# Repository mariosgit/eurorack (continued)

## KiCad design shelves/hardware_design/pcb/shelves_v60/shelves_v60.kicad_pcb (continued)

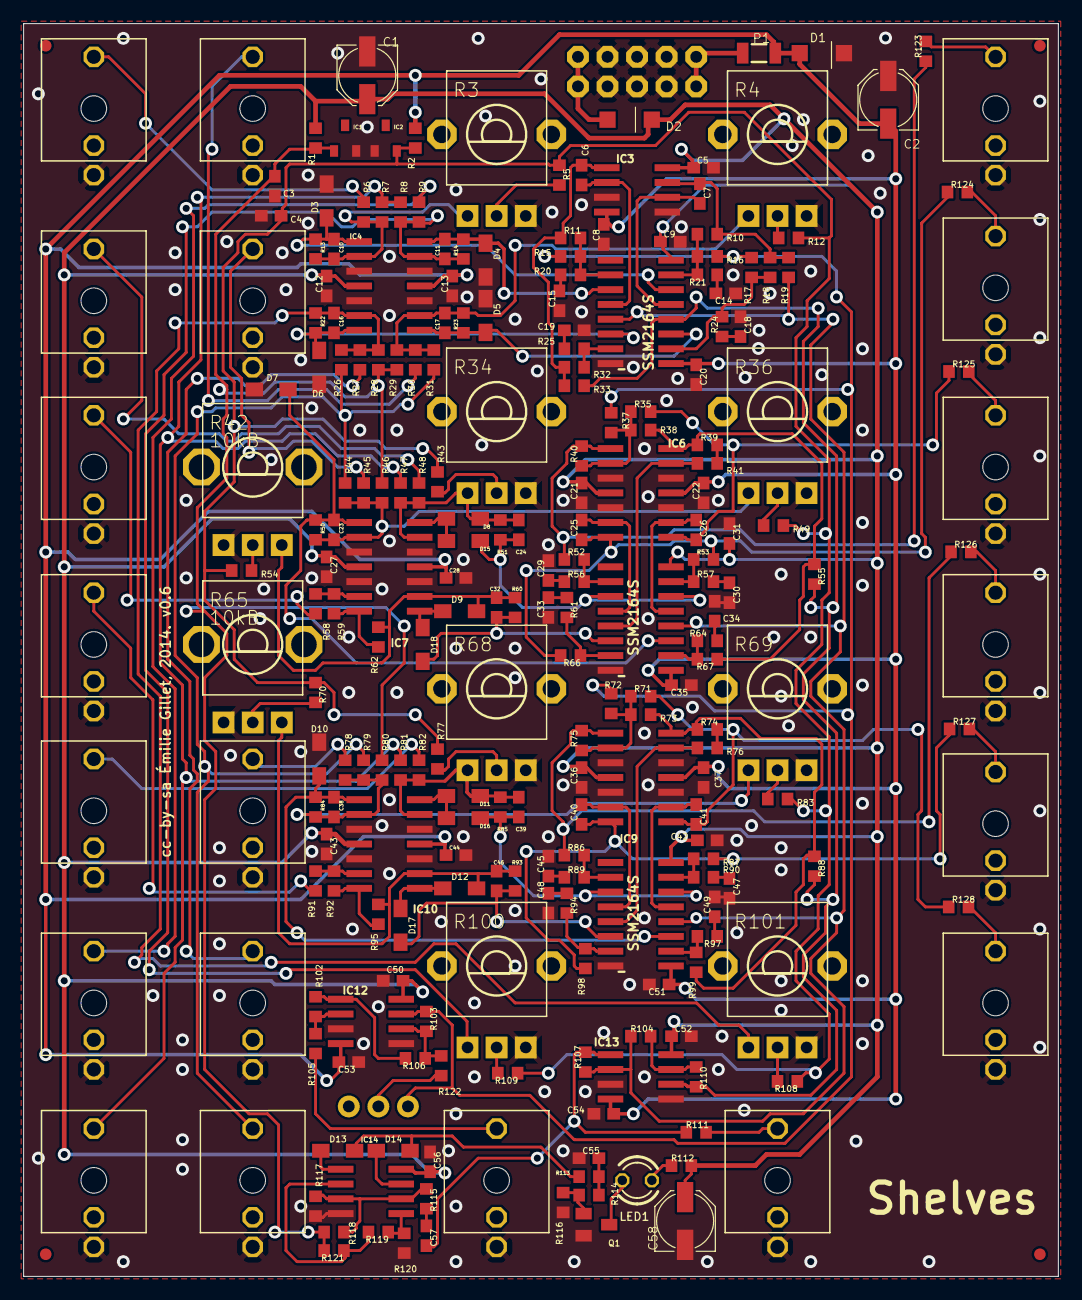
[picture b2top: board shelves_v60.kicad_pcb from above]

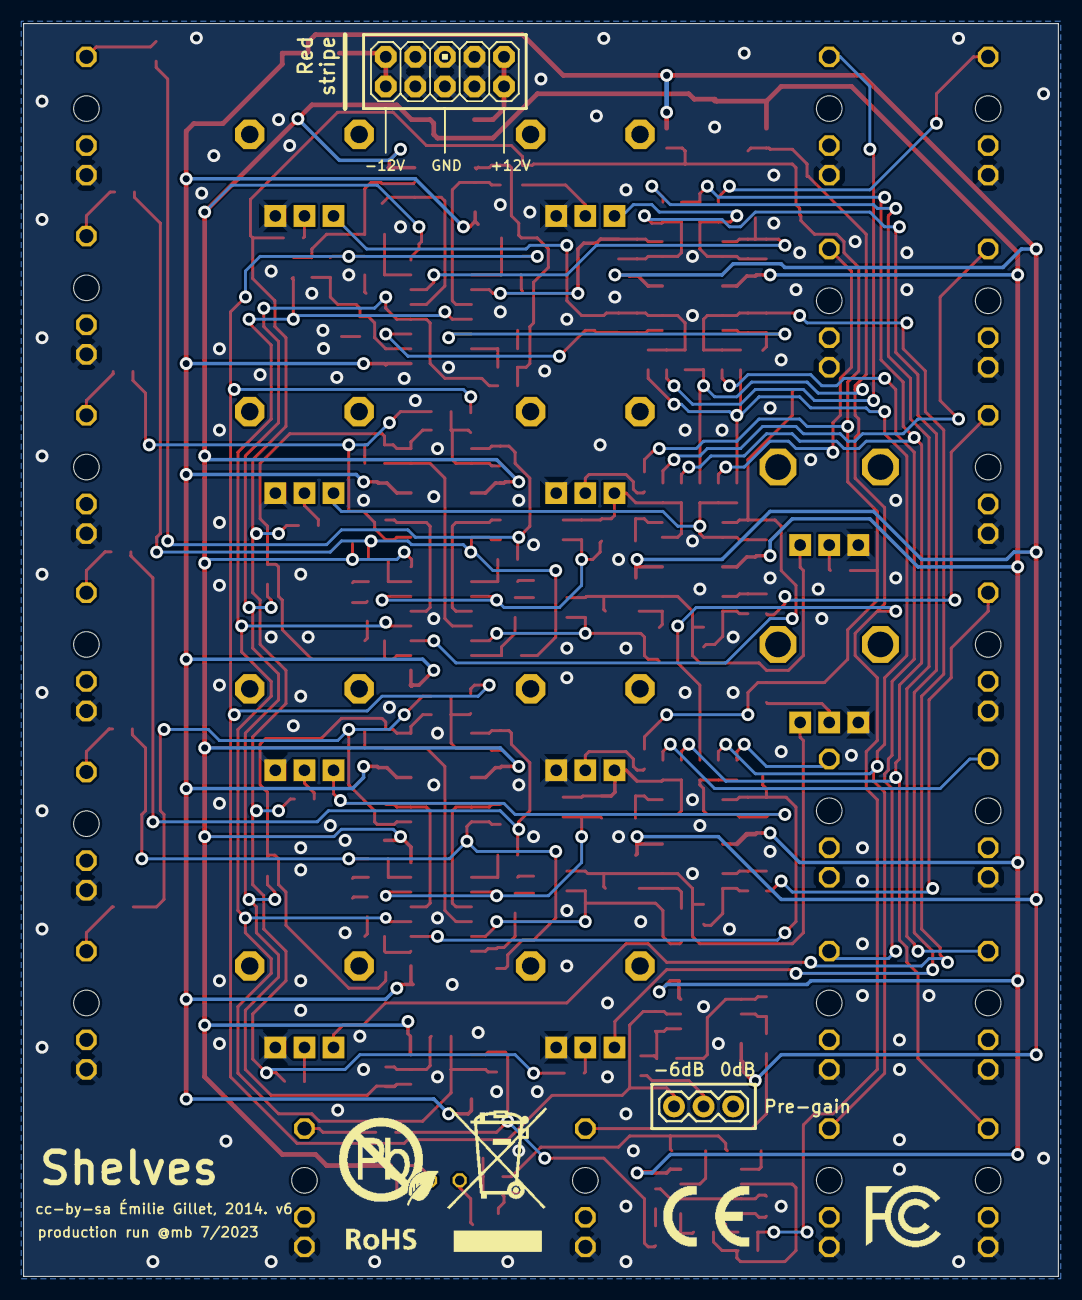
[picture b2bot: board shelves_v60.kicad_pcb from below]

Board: 2 copper layers, 88.9 x 107.6 mm, 248 parts (5 on the bottom side), 131 nets.

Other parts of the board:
U$1: FCC_MEDIUM
U$2: ROHS_BIG
U$3: CE_MEDIUM

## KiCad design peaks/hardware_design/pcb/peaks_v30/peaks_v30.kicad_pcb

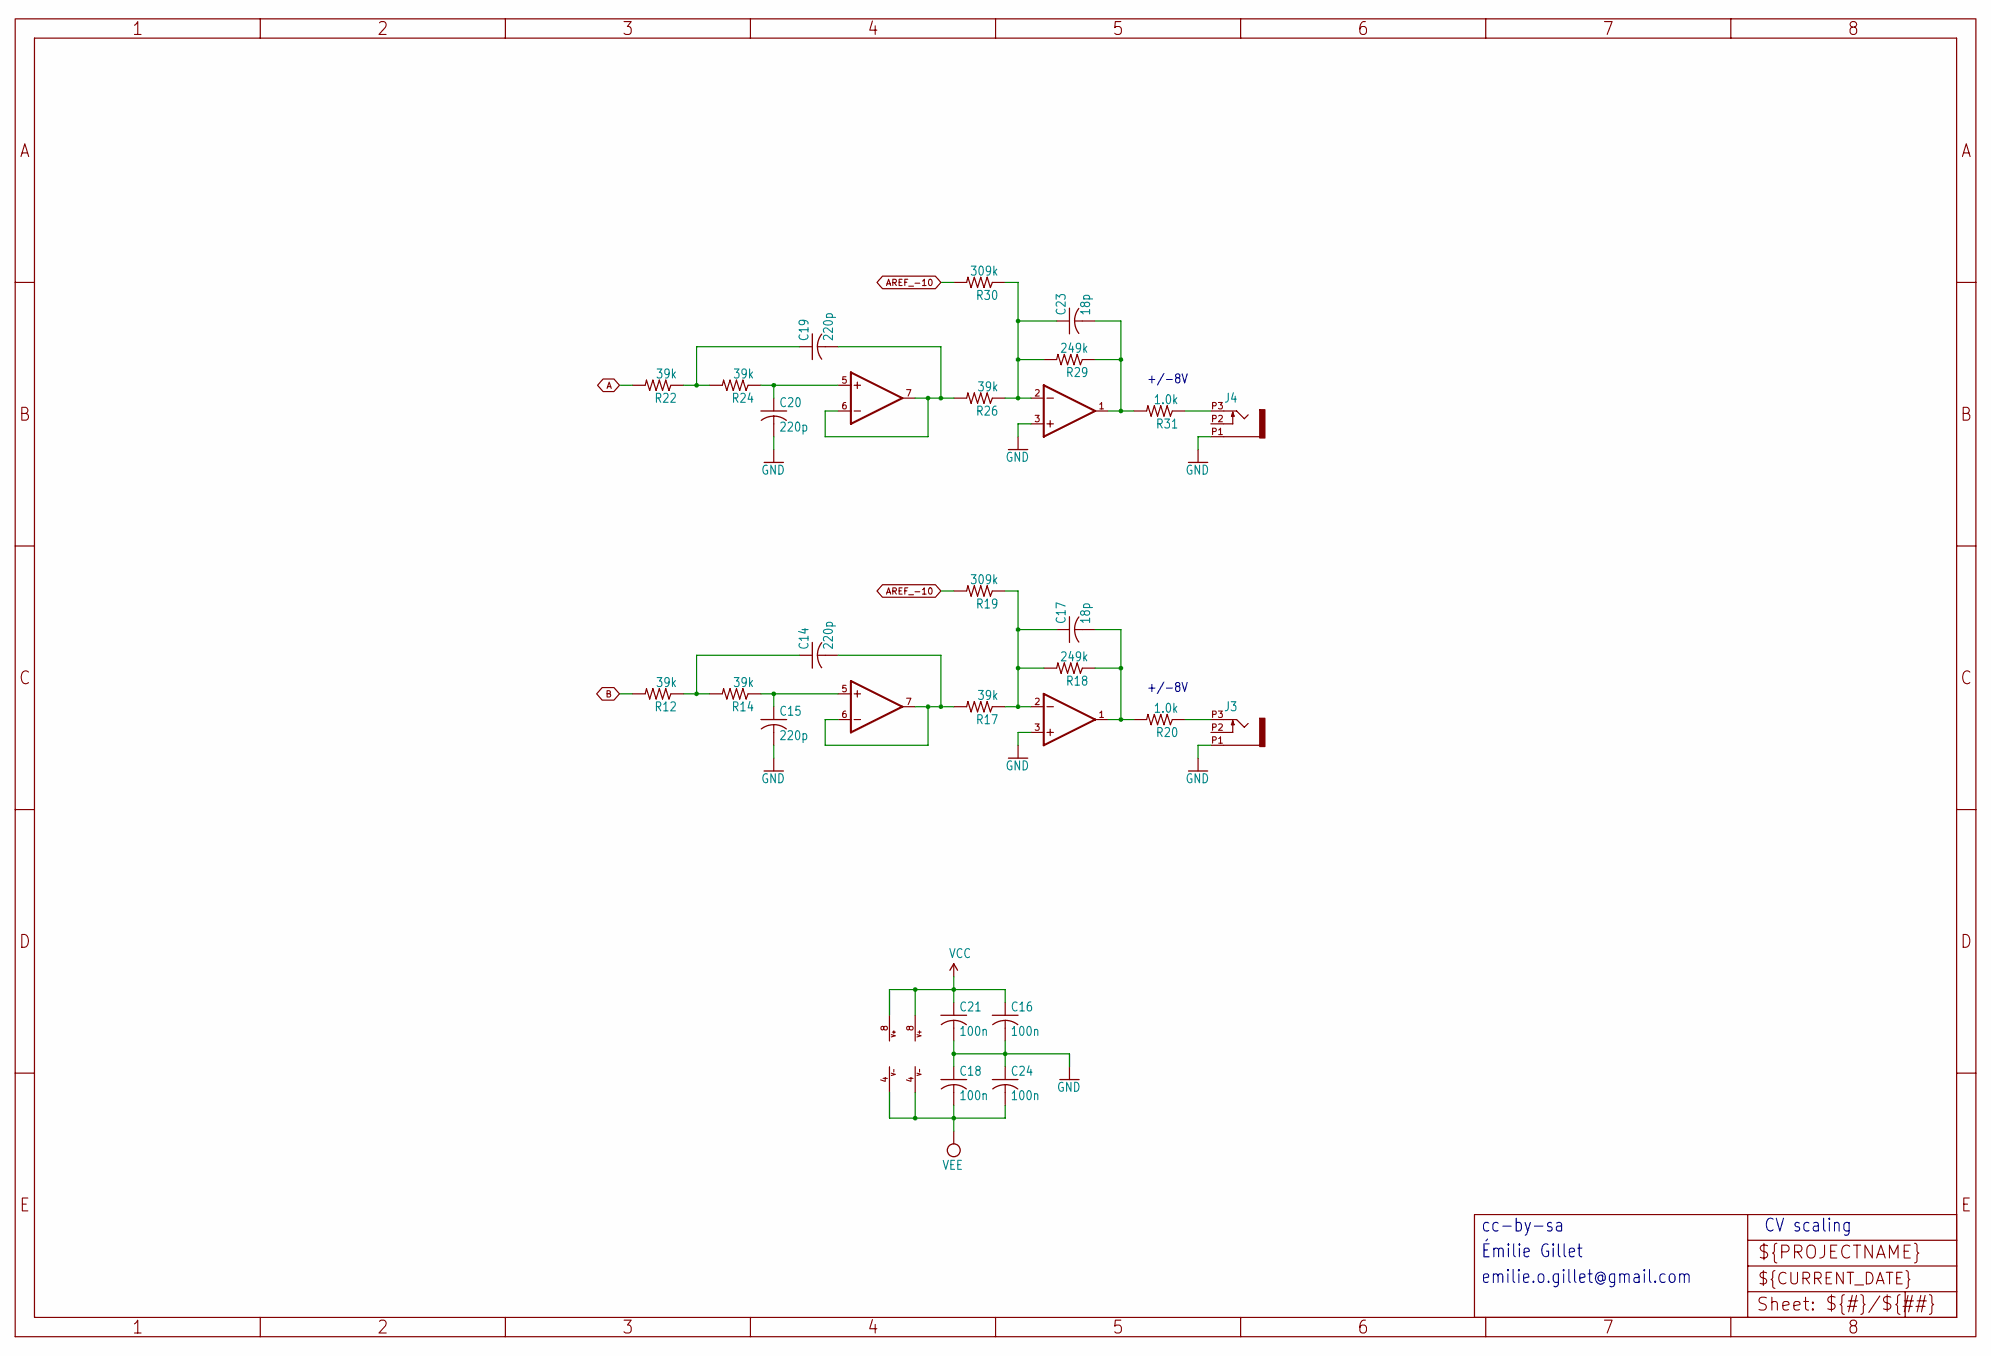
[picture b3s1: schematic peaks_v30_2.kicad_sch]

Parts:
C14, C15, C19, C20: 220p; C0603
C16, C18, C21, C24: 100n; C0603
C17, C23: 18p; C0603
IC4, IC5: TL072D; SO08
J3, J4: PJ301_THONKICONN6; WQP_PJ_301M6
R12, R14, R17, R22, R24, R26: 39k; R0603
R18, R29: 249k; R0603
R19, R30: 309k; R0603
R20, R31: 1.0k; R0603

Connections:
A: R22.2; also elsewhere on the board
AREF_-10: R19.2, R30.2; also elsewhere on the board
B: R12.2; also elsewhere on the board
GND: C15.2, C16.2, C18.1, C20.2, C21.2, C24.1, IC4.3 (+IN), IC5.3 (+IN), J3.P1 (1), J4.P1 (1); also elsewhere on the board
unnamed: C14.1, R12.1, R14.2
unnamed: C19.1, R22.1, R24.2
unnamed: C17.1, IC4.2 (-IN), R17.1, R18.2, R19.1
unnamed: C17.2, IC4.1 (OUT), R18.1, R20.2
unnamed: C15.1, IC4.5 (+IN), R14.1
unnamed: C14.2, IC4.6 (-IN), IC4.7 (OUT), R17.2
unnamed: C23.1, IC5.2 (-IN), R26.1, R29.2, R30.1
unnamed: C23.2, IC5.1 (OUT), R29.1, R31.2
unnamed: C20.1, IC5.5 (+IN), R24.1
unnamed: C19.2, IC5.6 (-IN), IC5.7 (OUT), R26.2
unnamed: J3.P3 (3), R20.1
unnamed: J4.P3 (3), R31.1
VCC: C16.1, C21.1, IC4.8 (V+), IC5.8 (V+); also elsewhere on the board
VEE: C18.2, C24.2, IC4.4 (V-), IC5.4 (V-); also elsewhere on the board

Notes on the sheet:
CV scaling
emilie.o.gillet@gmail.com
+/-8V
cc-by-sa
Émilie Gillet

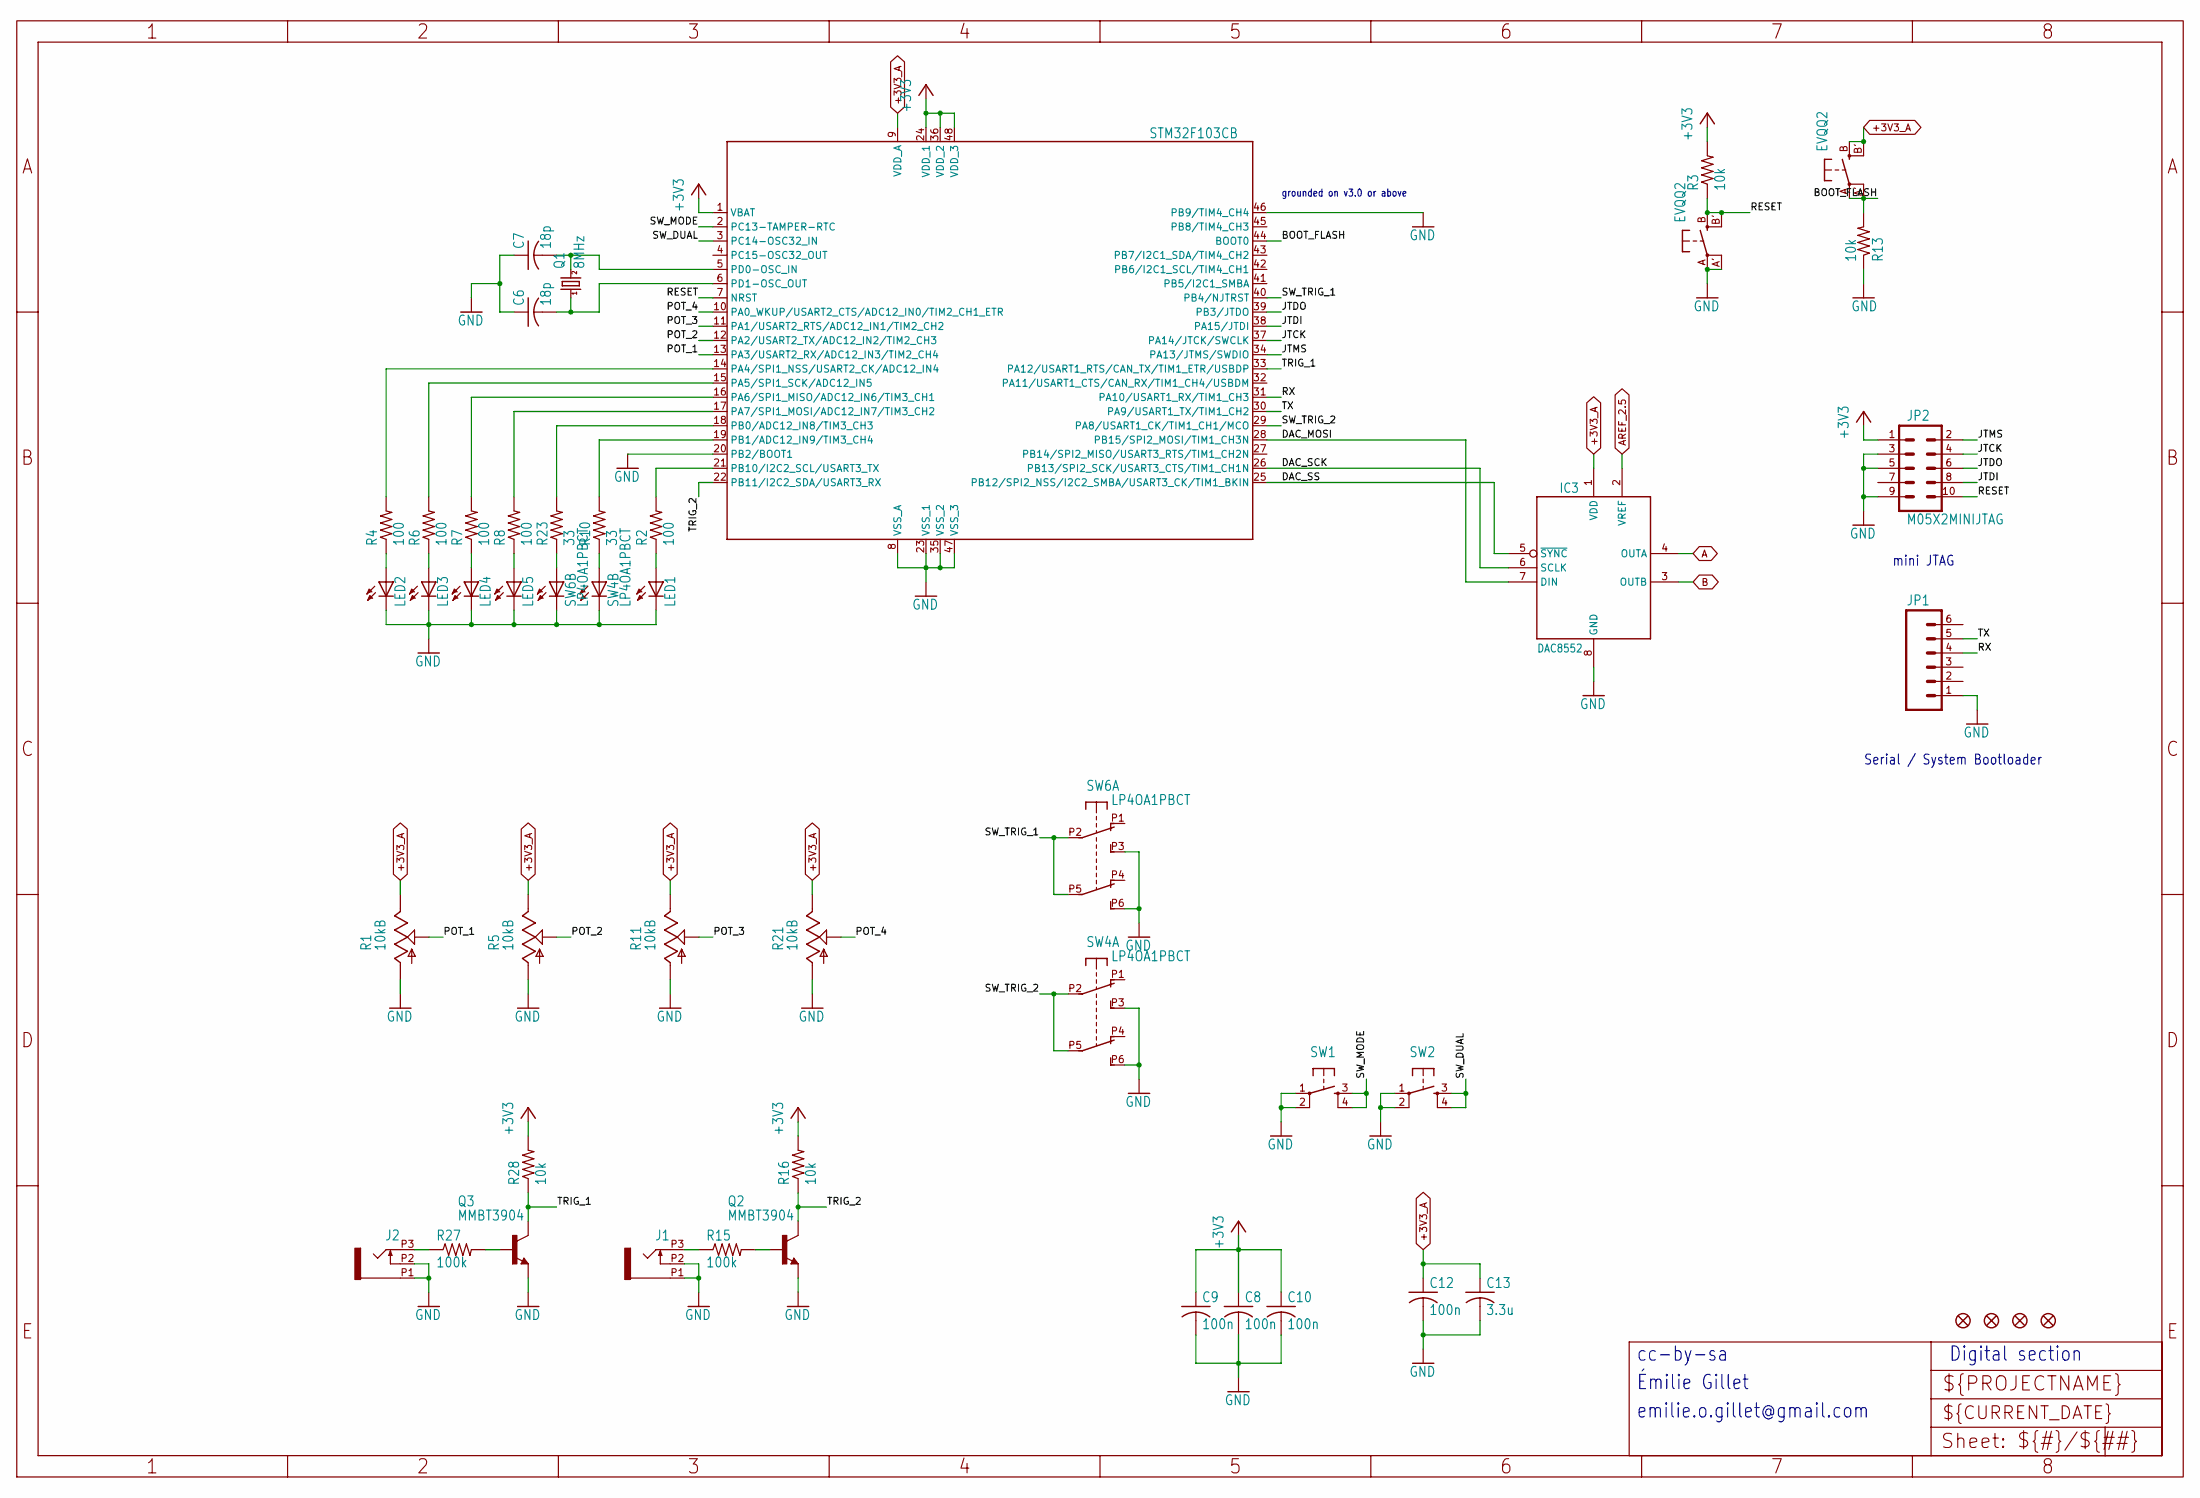
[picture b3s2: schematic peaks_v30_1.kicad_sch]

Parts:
C6, C7: 18p; C0603
C8, C9, C10, C12: 100n; C0603
C13: 3.3u; C0603
F1, F2, F3, F4: FIDUCIAL1X2; FIDUCIAL-1X2
IC3: DAC8552; MSOP-8
J1, J2: PJ301_THONKICONN6; WQP_PJ_301M6
JP1: M06SIP; 1X06
JP2: M05X2MINIJTAG; 2X5-1.27
LED1, LED2, LED3, LED4, LED5: LED3MM
Q1: 8MHz; HC49UP
Q2, Q3: MMBT3904; SOT23-BEC
R1, R5, R11, R21: 10kB; ALPS_POT_VERTICAL_PS
R2, R4, R6, R7, R8: 100; R0603
R3, R13, R16, R28: 10k; R0603
R10, R23: 33; R0603
R15, R27: 100k; R0603
SW1, SW2: TAC_SWITCHPTH; TACTILE-PTH
SW3, SW5: EVQQ2; EVQ-Q2
SW4, SW6: LP4OA1PBCT
UC1: STM32F103CB; LQFP48

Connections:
+3V3: C8.1, C9.1, C10.1, JP2.1, R3.2, R16.2, R28.2, UC1.1 (VBAT), UC1.24 (VDD_1), UC1.36 (VDD_2), UC1.48 (VDD_3); also elsewhere on the board
+3V3_A: C12.1, C13.1, IC3.1 (VDD), R1.P$1 (E), R5.P$1 (E), R11.P$1 (E), R21.P$1 (E), SW5.B (S), SW5.B' (S1), UC1.9 (VDD_A); also elsewhere on the board
/peaks_v30_1/BOOT_FLASH: R13.2, SW5.A, SW5.A' (P1), UC1.44 (BOOT0)
/peaks_v30_1/DAC_MOSI: IC3.7 (DIN), UC1.28 (PB15/SPI2_MOSI/TIM1_CH3N)
/peaks_v30_1/DAC_SCK: IC3.6 (SCLK), UC1.26 (PB13/SPI2_SCK/USART3_CTS/TIM1_CH1N)
/peaks_v30_1/DAC_SS: IC3.5 (~SYNC), UC1.25 (PB12/SPI2_NSS/I2C2_SMBA/USART3_CK/TIM1_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)
/peaks_v30_1/JTCK: JP2.4, UC1.37 (PA14/JTCK/SWCLK)
/peaks_v30_1/JTDI: JP2.8, UC1.38 (PA15/JTDI)
/peaks_v30_1/JTDO: JP2.6, UC1.39 (PB3/JTDO)
/peaks_v30_1/JTMS: JP2.2, UC1.34 (PA13/JTMS/SWDIO)
/peaks_v30_1/POT_1: R1.P$2 (S), UC1.13 (PA3/USART2_RX/ADC12_IN3/TIM2_CH4)
/peaks_v30_1/POT_2: R5.P$2 (S), UC1.12 (PA2/USART2_TX/ADC12_IN2/TIM2_CH3)
/peaks_v30_1/POT_3: R11.P$2 (S), UC1.11 (PA1/USART2_RTS/ADC12_IN1/TIM2_CH2)
/peaks_v30_1/POT_4: R21.P$2 (S), UC1.10 (PA0_WKUP/USART2_CTS/ADC12_IN0/TIM2_CH1_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)
/peaks_v30_1/RESET: JP2.10, R3.1, SW3.B (S), SW3.B' (S1), UC1.7 (NRST)
/peaks_v30_1/RX: JP1.4, UC1.31 (PA10/USART1_RX/TIM1_CH3)
/peaks_v30_1/SW_DUAL: SW2.3, SW2.4, UC1.3 (PC14-OSC32_IN)
/peaks_v30_1/SW_MODE: SW1.3, SW1.4, UC1.2 (PC13-TAMPER-RTC)
/peaks_v30_1/SW_TRIG_1: SW6.P2 (A2), SW6.P5 (B2), UC1.40 (PB4/NJTRST)
/peaks_v30_1/SW_TRIG_2: SW4.P2 (A2), SW4.P5 (B2), UC1.29 (PA8/USART1_CK/TIM1_CH1/MCO)
/peaks_v30_1/TRIG_1: Q3.C, R28.1, UC1.33 (PA12/USART1_RTS/CAN_TX/TIM1_ETR/USBDP)
/peaks_v30_1/TRIG_2: Q2.C, R16.1, UC1.22 (PB11/I2C2_SDA/USART3_RX)
/peaks_v30_1/TX: JP1.5, UC1.30 (PA9/USART1_TX/TIM1_CH2)
A: IC3.4 (OUTA); also elsewhere on the board
AREF_2.5: IC3.2 (VREF); also elsewhere on the board
B: IC3.3 (OUTB); also elsewhere on the board
GND: C6.1, C7.1, C8.2, C9.2, C10.2, C12.2, C13.2, IC3.8 (GND), J1.P1 (1), J1.P2 (2), J2.P1 (1), J2.P2 (2), JP1.1, JP2.3, JP2.5, JP2.9, LED1.K (C), LED2.K (C), LED3.K (C), LED4.K (C), LED5.K (C), Q2.E, Q3.E, R1.P$3 (A), R5.P$3 (A), R11.P$3 (A), R13.1, R21.P$3 (A), SW1.1, SW1.2, SW2.1, SW2.2, SW3.A, SW3.A' (P1), SW4.L2, SW4.P3 (A3), SW4.P6 (B3), SW6.L2, SW6.P3 (A3), SW6.P6 (B3), UC1.8 (VSS_A), UC1.20 (PB2/BOOT1), UC1.23 (VSS_1), UC1.35 (VSS_2), UC1.46 (PB9/TIM4_CH4), UC1.47 (VSS_3); also elsewhere on the board
unnamed: J1.P3 (3), R15.1
unnamed: J2.P3 (3), R27.1
unnamed: LED1.A, R2.1
unnamed: LED2.A, R4.1
unnamed: LED3.A, R6.1
unnamed: LED4.A, R7.1
unnamed: LED5.A, R8.1
unnamed: Q2.B, R15.2
unnamed: Q3.B, R27.2
unnamed: R10.1, SW4.L1
unnamed: R23.1, SW6.L1
unnamed: R4.2, UC1.14 (PA4/SPI1_NSS/USART2_CK/ADC12_IN4)
unnamed: R6.2, UC1.15 (PA5/SPI1_SCK/ADC12_IN5)
unnamed: R7.2, UC1.16 (PA6/SPI1_MISO/ADC12_IN6/TIM3_CH1)
unnamed: R8.2, UC1.17 (PA7/SPI1_MOSI/ADC12_IN7/TIM3_CH2)
unnamed: R23.2, UC1.18 (PB0/ADC12_IN8/TIM3_CH3)
unnamed: R10.2, UC1.19 (PB1/ADC12_IN9/TIM3_CH4)
unnamed: R2.2, UC1.21 (PB10/I2C2_SCL/USART3_TX)
unnamed: C7.2, Q1.2, UC1.5 (PD0-OSC_IN)
unnamed: C6.2, Q1.1, UC1.6 (PD1-OSC_OUT)

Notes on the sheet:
Digital section
cc-by-sa
Émilie Gillet
emilie.o.gillet@gmail.com
Serial / System Bootloader
mini JTAG
grounded on v3.0 or above

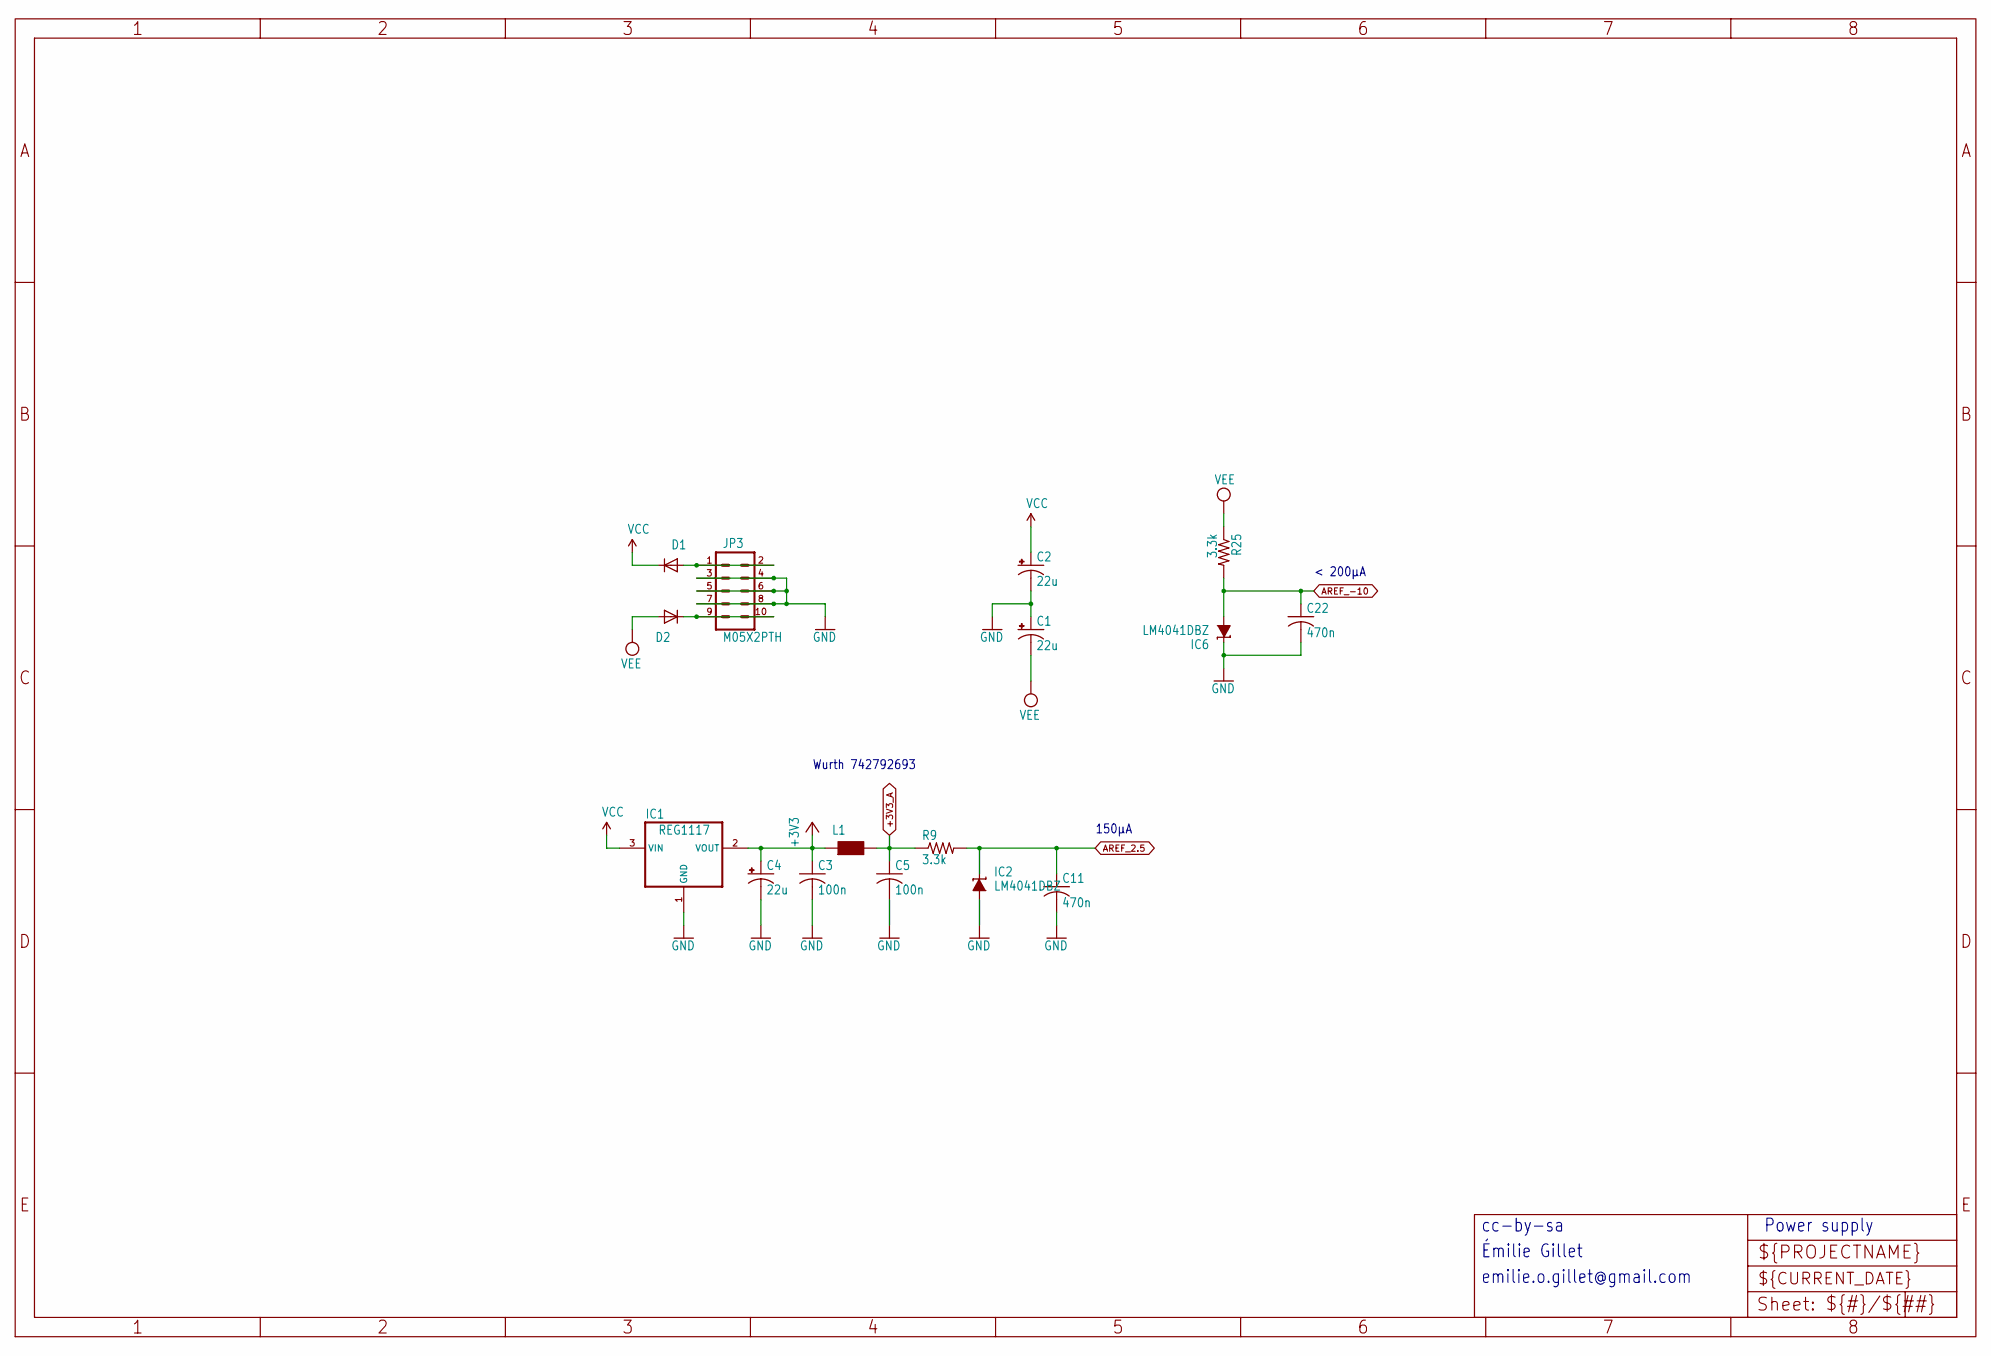
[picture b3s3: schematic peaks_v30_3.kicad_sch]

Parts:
C1, C2, C4: 22u; PANASONIC_C
C3, C5: 100n; C0603
C11, C22: 470n; C0603
D1, D2: 1N5819HW; SOD123
IC1: REG1117; SOT223
IC2, IC6: LM4041DBZ; DBZ_R-PDSO-G3
JP3: M05X2PTH; AVR_ICSP
L1: WE-CBF_0603; 0603
R9, R25: 3.3k; R0603

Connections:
+3V3: C3.1, C4.+, IC1.2 (VOUT), L1.1; also elsewhere on the board
+3V3_A: C5.1, L1.2, R9.1; also elsewhere on the board
AREF_2.5: C11.1, IC2.1 (C), R9.2; also elsewhere on the board
AREF_-10: C22.1, IC6.2 (A), R25.2; also elsewhere on the board
GND: C1.+, C2.-, C3.2, C4.-, C5.2, C11.2, C22.2, IC1.1 (GND), IC2.2 (A), IC6.1 (C), JP3.3, JP3.4, JP3.5, JP3.6, JP3.7, JP3.8; also elsewhere on the board
unnamed: D1.A, JP3.1, JP3.2
unnamed: D2.C, JP3.9, JP3.10
VCC: C2.+, D1.C, IC1.3 (VIN); also elsewhere on the board
VEE: C1.-, D2.A, R25.1; also elsewhere on the board

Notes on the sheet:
Émilie Gillet
Wurth 742792693
Power supply
150µA
cc-by-sa
emilie.o.gillet@gmail.com
< 200µA

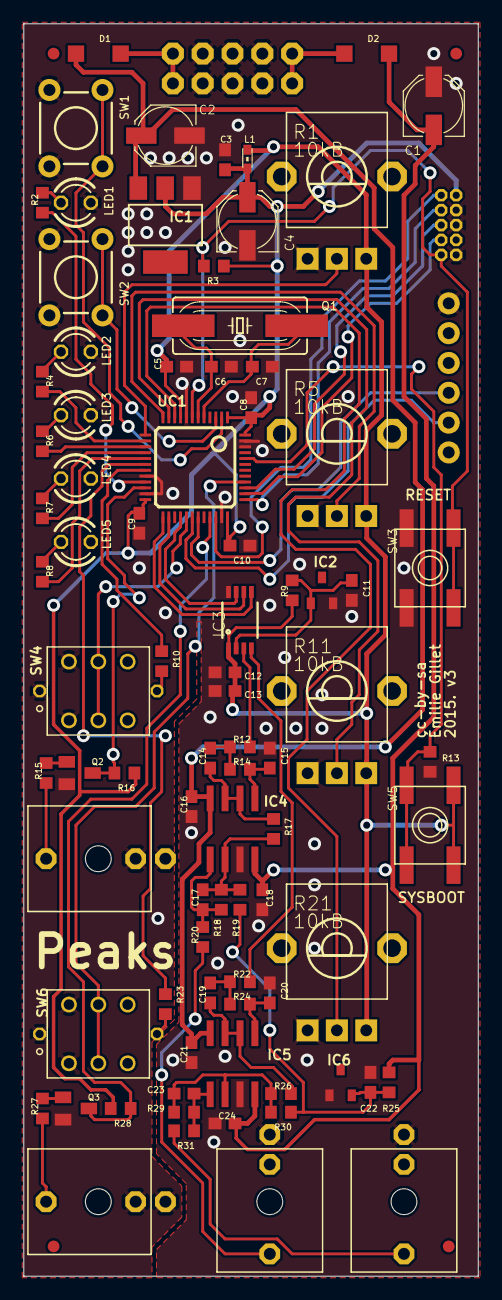
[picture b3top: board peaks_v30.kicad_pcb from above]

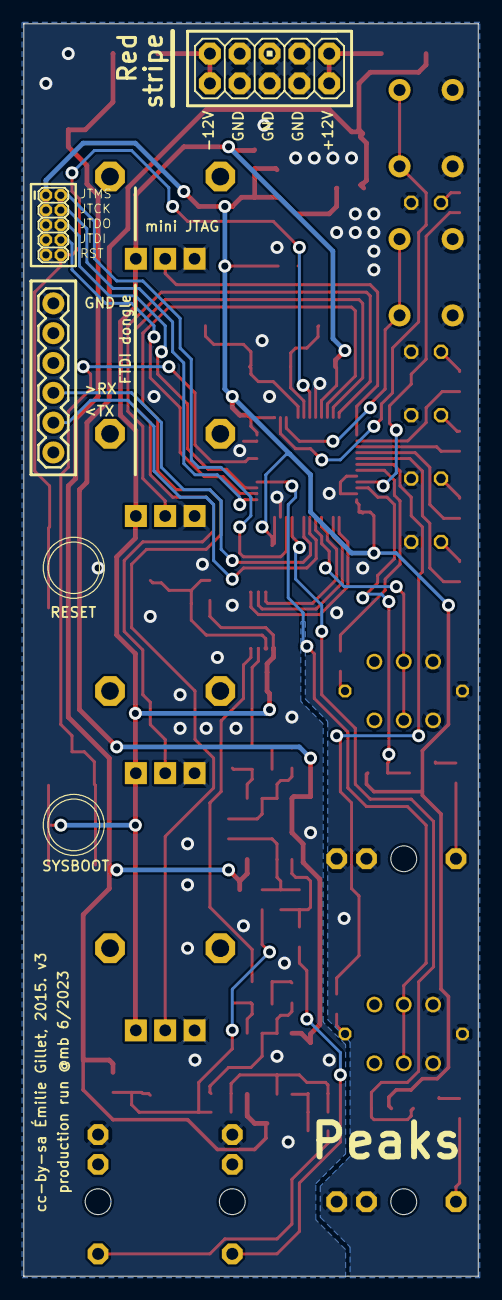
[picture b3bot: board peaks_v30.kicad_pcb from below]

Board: 2 copper layers, 38.7 x 106.7 mm, 90 parts (3 on the bottom side), 64 nets.

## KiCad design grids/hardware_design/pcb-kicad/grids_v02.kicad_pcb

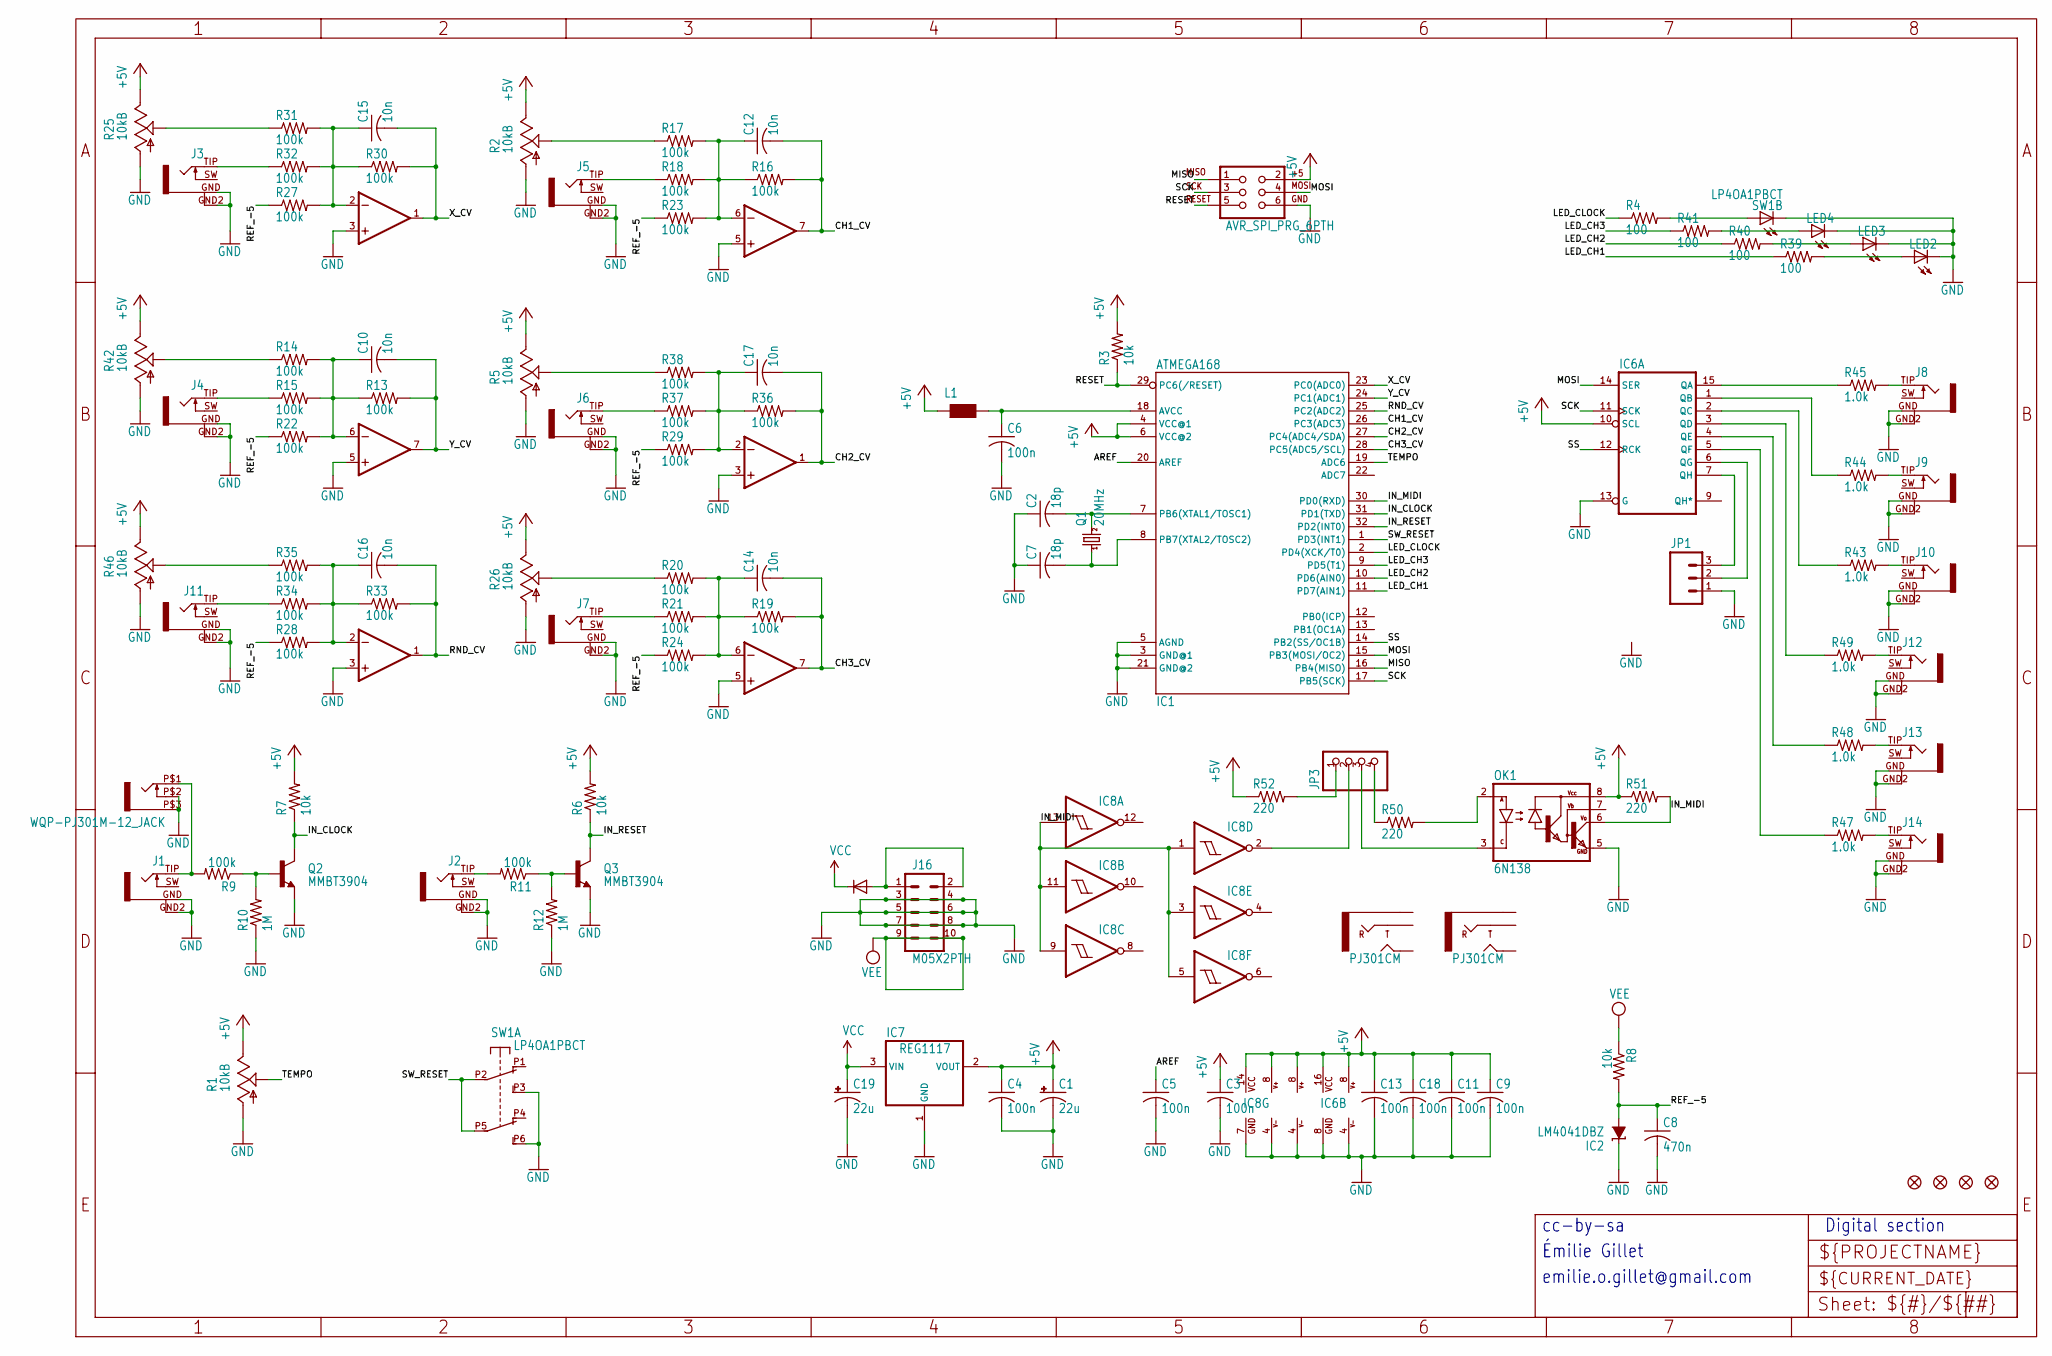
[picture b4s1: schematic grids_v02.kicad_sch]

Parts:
C1, C19: 22u; PANASONIC_C
C2, C7: 18p; C0603
C3, C4, C5, C6, C9, C11, C13, C18: 100n; C0603
C8: 470n; C0603
C10, C12, C14, C15, C16, C17: 10n; C0603
D1: 1N5819HW; SOD123
F1, F2, F3, F4: FIDUCIAL1X2; FIDUCIAL-1X2
IC1: ATMEGA168; TQFP32-08
IC2: LM4041DBZ; DBZ_R-PDSO-G3
IC3, IC4, IC5: TL072D; SO08
IC6: 74595D; SO16
IC7: REG1117; SOT223
IC8: 7414D; SO14
J1, J2, J3, J4, J5, J6, J7, J8, J9, J10, J11, J12, J13, J14: PJ301WQP; WQP_PJ_301BM
J15: AVR_SPI_PRG_6PTH; 2X3
J16: M05X2PTH; AVR_ICSP
JP1: M03PTH; 1X03
JP3: PINHD-1X4; 1X04
L1: WE-CBF_0603; 0603
LED2, LED3, LED4: LED3MM
OK1: 6N138; DIL08
Q1: 20MHz; HC49UP
Q2, Q3: MMBT3904; SOT23-BEC
R1, R2, R5, R25, R26, R46: 10kB; ALPS_POT_VERTICAL_PS
R3, R6, R7, R8: 10k; R0603
R4, R39, R40, R41: 100; R0603
R9, R11, R13, R14, R15, R16, R17, R18, R19, R20, R21, R22, R23, R24, R27, R28, R29, R30, R31, R32, R33, R34, R35, R36, R37, R38: 100k; R0603
R10, R12: 1M; R0603
R42: 10kB; ALPS_POT_VERTICAL_PS4
R43, R44, R45, R47, R48, R49: 1.0k; R0603
R50, R51, R52: 220; R0603
SW1: LP4OA1PBCT
U$1, U$3: PJ301CM
U$4: WQP-PJ301M-12_JACK

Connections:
+5V: C1.+, C3.1, C4.1, C9.1, C11.1, C13.1, C18.1, IC1.4 (VCC@1), IC1.6 (VCC@2), IC3.8 (V+), IC4.8 (V+), IC5.8 (V+), IC6.10 (SCL), IC6.16 (VCC), IC7.2 (VOUT), IC8.14 (VCC), J15.2, L1.1, OK1.8 (VCC), R1.P$1 (E), R2.P$1 (E), R3.2, R5.P$1 (E), R6.2, R7.2, R25.P$1 (E), R26.P$1 (E), R42.P$1 (E), R46.P$1 (E), R51.1, R52.1
AREF: C5.1, IC1.20 (AREF)
CH1_CV: C12.2, IC1.26 (PC3(ADC3)), IC4.7 (OUT), R16.2
CH2_CV: C17.2, IC1.27 (PC4(ADC4/SDA)), IC5.1 (OUT), R36.2
CH3_CV: C14.2, IC1.28 (PC5(ADC5/SCL)), IC5.7 (OUT), R19.2
CLOCK_OUT: IC6.6 (QG), JP1.2
GATE1_IN: J1.TIP (2), R9.2, U$4.P$1 (2)
GATE1_LED: R4.2, SW1.L1
GATE2_IN: J2.TIP (2), R11.2
GATE2_LED: LED4.A, R41.2
GATE3_LED: LED3.A, R40.2
GATE4_LED: LED2.A, R39.2
GND: C1.-, C2.1, C3.2, C4.2, C5.2, C6.2, C7.1, C8.2, C9.2, C11.2, C13.2, C18.2, C19.-, IC1.3 (GND@1), IC1.5 (AGND), IC1.21 (GND@2), IC2.1 (C), IC3.3 (+IN), IC3.4 (V-), IC3.5 (+IN), IC4.3 (+IN), IC4.4 (V-), IC4.5 (+IN), IC5.3 (+IN), IC5.4 (V-), IC5.5 (+IN), IC6.8 (GND), IC6.13 (G), IC7.1 (GND), IC8.7 (GND), J1.GND (1), J1.GND2 (4), J2.GND (1), J2.GND2 (4), J3.GND (1), J3.GND2 (4), J4.GND (1), J4.GND2 (4), J5.GND (1), J5.GND2 (4), J6.GND (1), J6.GND2 (4), J7.GND (1), J7.GND2 (4), J8.GND (1), J8.GND2 (4), J9.GND (1), J9.GND2 (4), J10.GND (1), J10.GND2 (4), J11.GND (1), J11.GND2 (4), J12.GND (1), J12.GND2 (4), J13.GND (1), J13.GND2 (4), J14.GND (1), J14.GND2 (4), J15.6, J16.3, J16.4, J16.5, J16.6, J16.7, J16.8, JP1.1, LED2.K (C), LED3.K (C), LED4.K (C), OK1.5 (GND), Q2.E, Q3.E, R1.P$3 (A), R2.P$3 (A), R5.P$3 (A), R10.1, R12.1, R25.P$3 (A), R26.P$3 (A), R42.P$3 (A), R46.P$3 (A), SW1.L2, SW1.P3 (A3), SW1.P6 (B3), U$4.P$2 (3), U$4.P$3 (1)
IN_CLOCK: IC1.31 (PD1(TXD)), Q2.C, R7.1
IN_MIDI: IC1.30 (PD0(RXD)), IC8.1 (I), IC8.3 (I), IC8.5 (I), IC8.9 (I), IC8.11 (I), IC8.13 (I), OK1.6 (VO), R51.2
IN_RESET: IC1.32 (PD2(INT0)), Q3.C, R6.1
LED_CH1: IC1.11 (PD7(AIN1)), R39.1
LED_CH2: IC1.10 (PD6(AIN0)), R40.1
LED_CH3: IC1.9 (PD5(T1)), R41.1
LED_CLOCK: IC1.2 (PD4(XCK/T0)), R4.1
MISO: IC1.16 (PB4(MISO)), J15.1
MOSI: IC1.15 (PB3(MOSI/OC2)), IC6.14 (SER), J15.4
unnamed: Q2.B, R9.1, R10.2
unnamed: Q3.B, R11.1, R12.2
unnamed: D1.A, J16.1, J16.2
unnamed: J14.TIP (2), R47.2
unnamed: J13.TIP (2), R48.2
unnamed: J12.TIP (2), R49.2
unnamed: R25.P$2 (S), R31.1
unnamed: J3.TIP (2), R32.1
unnamed: C10.1, IC3.6 (-IN), R13.1, R14.2, R15.2, R22.2
unnamed: R14.1, R42.P$2 (S)
unnamed: J4.TIP (2), R15.1
unnamed: C16.1, IC4.2 (-IN), R28.2, R33.1, R34.2, R35.2
unnamed: R35.1, R46.P$2 (S)
unnamed: J11.TIP (2), R34.1
unnamed: C12.1, IC4.6 (-IN), R16.1, R17.2, R18.2, R23.2
unnamed: R2.P$2 (S), R17.1
unnamed: J5.TIP (2), R18.1
unnamed: C17.1, IC5.2 (-IN), R29.2, R36.1, R37.2, R38.2
unnamed: R5.P$2 (S), R38.1
unnamed: J6.TIP (2), R37.1
unnamed: C14.1, IC5.6 (-IN), R19.1, R20.2, R21.2, R24.2
unnamed: R20.1, R26.P$2 (S)
unnamed: J7.TIP (2), R21.1
unnamed: IC6.15 (QA), R45.1
unnamed: IC6.1 (QB), R44.1
unnamed: C15.1, IC3.2 (-IN), R27.2, R30.1, R31.2, R32.2
unnamed: IC6.2 (QC), R43.1
unnamed: IC6.3 (QD), R49.1
unnamed: IC6.4 (QE), R48.1
unnamed: IC6.5 (QF), R47.1
unnamed: J8.TIP (2), R45.2
unnamed: J9.TIP (2), R44.2
unnamed: J10.TIP (2), R43.2
unnamed: C6.1, IC1.18 (AVCC), L1.2
unnamed: JP3.1, R52.2
unnamed: IC8.2 (O), JP3.2
unnamed: OK1.2 (A), R50.2
unnamed: JP3.3, OK1.3 (C)
unnamed: JP3.4, R50.1
unnamed: C7.2, IC1.8 (PB7(XTAL2/TOSC2)), Q1.1
unnamed: C2.2, IC1.7 (PB6(XTAL1/TOSC1)), Q1.2
RANDOM_GATE: IC6.7 (QH), JP1.3
REF_-5: C8.1, IC2.2 (A), R8.2, R22.1, R23.1, R24.1, R27.1, R28.1, R29.1
RESET: IC1.29 (PC6(/RESET)), J15.5, R3.1
RND_CV: C16.2, IC1.25 (PC2(ADC2)), IC4.1 (OUT), R33.2
SCK: IC1.17 (PB5(SCK)), IC6.11 (SCK), J15.3
SS: IC1.14 (PB2(SS/OC1B)), IC6.12 (RCK)
SW_RESET: IC1.1 (PD3(INT1)), SW1.P2 (A2), SW1.P5 (B2)
TEMPO: IC1.19 (ADC6), R1.P$2 (S)
VCC: C19.+, D1.C, IC7.3 (VIN)
VEE: J16.9, J16.10, R8.1
X_CV: C15.2, IC1.23 (PC0(ADC0)), IC3.1 (OUT), R30.2
Y_CV: C10.2, IC1.24 (PC1(ADC1)), IC3.7 (OUT), R13.2

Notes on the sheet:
emilie.o.gillet@gmail.com
Digital section
cc-by-sa
Émilie Gillet
